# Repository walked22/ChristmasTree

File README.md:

Christmas tree ornament gift

Features
- Powered by 3V coin cell battery
- Lights turn on and off in a circular pattern around the edge of the tree when the button is pressed
- Designed for Green and Red LEDs

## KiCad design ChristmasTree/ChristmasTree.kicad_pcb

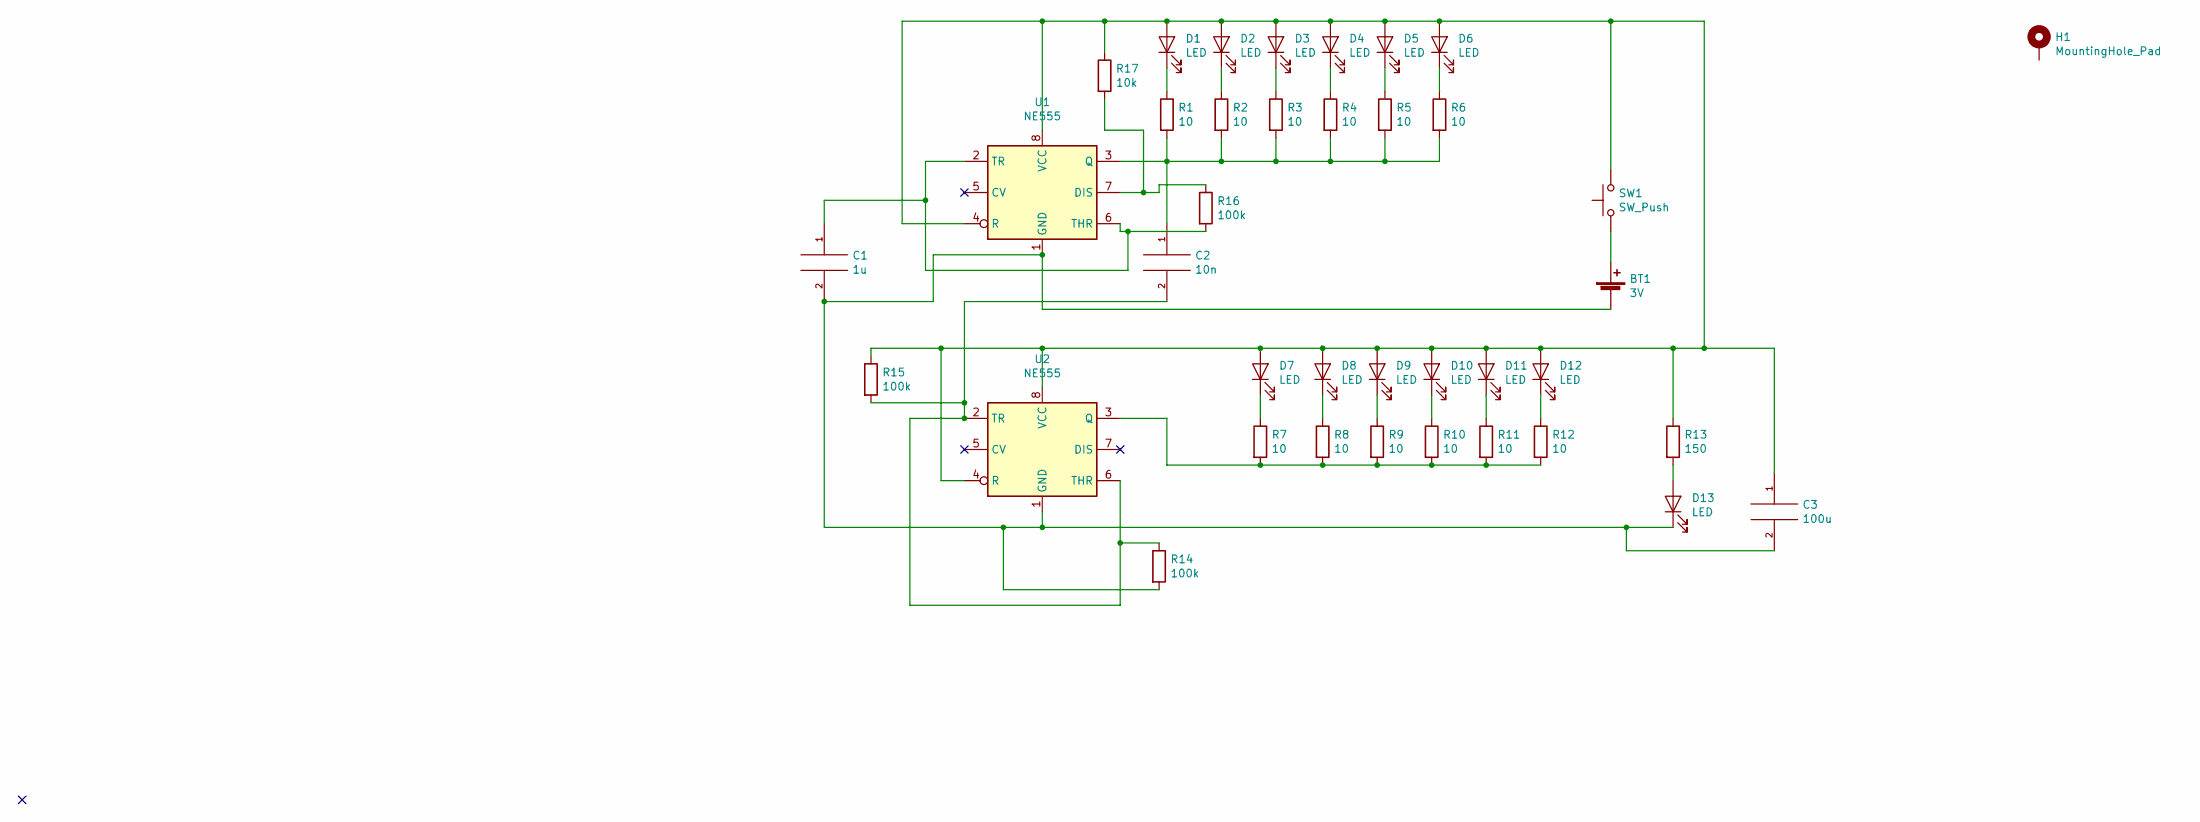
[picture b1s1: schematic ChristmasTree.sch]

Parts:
BT1: 3V; BatteryHolder_Keystone_3002_1x2032
C1: 1u; C_0805_2012Metric
C2: 10n; C_0805_2012Metric
C3: 100u; C_0805_2012Metric
D1, D2, D3, D4, D5, D6, D7, D8, D9, D10, D11, D12, D13: LED; LED_0805_2012Metric
H1: MountingHole_Pad; MountingHole_2.5mm_Pad_Via
R1, R2, R3, R4, R5, R6, R7, R8, R9, R10, R11, R12: 10; R_0805_2012Metric
R13: 150; R_0805_2012Metric
R14, R15, R16: 100k; R_0805_2012Metric
R17: 10k; R_0805_2012Metric
SW1: SW_Push; SW_SPST_B3S-1000
U1, U2: NE555; SOIC127P600X175-8N

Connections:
unnamed: BT1.1 (+), SW1.1
unnamed: BT1.2 (-), C1.2, C3.2, D13.1 (K), R14.2, U1.1 (GND), U2.1 (GND)
unnamed: C1.1, R16.2, U1.2 (TR), U1.6 (THR)
unnamed: C2.1, R1.2, R2.2, R3.2, R4.2, R5.2, R6.2, U1.3 (Q)
unnamed: C2.2, R14.1, R15.2, U2.2 (TR), U2.6 (THR)
unnamed: C3.1, D1.2 (A), D2.2 (A), D3.2 (A), D4.2 (A), D5.2 (A), D6.2 (A), D7.2 (A), D8.2 (A), D9.2 (A), D10.2 (A), D11.2 (A), D12.2 (A), R13.1, R15.1, R17.1, SW1.2, U1.4 (R), U1.8 (VCC), U2.4 (R), U2.8 (VCC)
unnamed: D1.1 (K), R1.1
unnamed: D2.1 (K), R2.1
unnamed: D3.1 (K), R3.1
unnamed: D4.1 (K), R4.1
unnamed: D5.1 (K), R5.1
unnamed: D6.1 (K), R6.1
unnamed: D7.1 (K), R7.1
unnamed: D8.1 (K), R8.1
unnamed: D9.1 (K), R9.1
unnamed: D10.1 (K), R10.1
unnamed: D11.1 (K), R11.1
unnamed: D12.1 (K), R12.1
unnamed: D13.2 (A), R13.2
unnamed: R7.2, R8.2, R9.2, R10.2, R11.2, R12.2, U2.3 (Q)
unnamed: R16.1, R17.2, U1.7 (DIS)

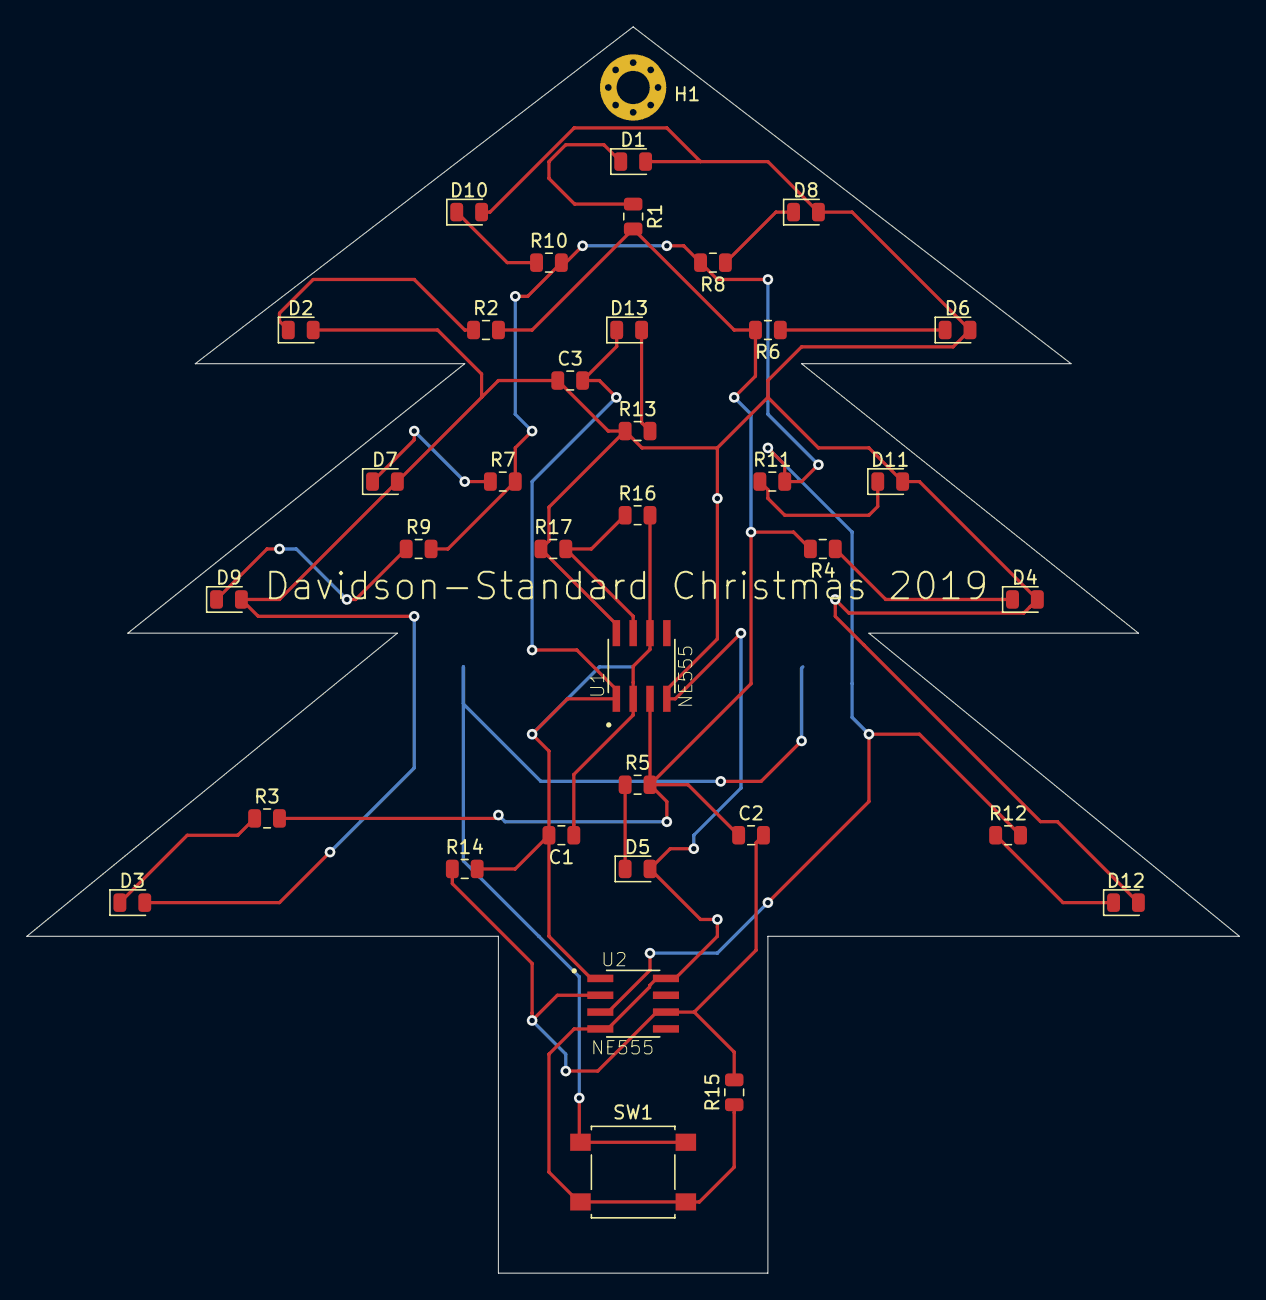
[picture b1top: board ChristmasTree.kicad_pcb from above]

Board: 2 copper layers, 91.4 x 94.0 mm, 38 parts (1 on the bottom side), 21 nets.

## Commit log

2019-12-12 First version of christmas tree gift
2019-12-12 Ignore gbr and drl
2019-12-12 Removed gbr files
2019-12-12 removed backups from git
2019-12-12 added images of board
2019-12-12 Created Readme
